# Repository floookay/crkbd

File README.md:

# Corne keyboard fork

The Corne keyboard is a split keyboard with 3x6 column staggered keys and 3 thumb keys,
based on [Helix](https://github.com/MakotoKurauchi/helix).
Crkbd stands for Corne Keyboard.

## Corne MX Low Profile

This fork altered the footprints of the Corne Classic to support Cherry MX Low Profile switches.  
For more information on how to build one see [here](./corne-mxlp/doc/buildguide_en.md)

### Compability

Despite the MX style stem of the switches these are not compatible with every MX style keycap. I included some more information in the build guide.

### RGB

The switches route the light of the RGB LEDs quite nicely imo: <https://imgur.com/7JVrjXo>

### PCB

I designed the footprint for the MXLP switch based on my measurements. The footprint file is included with the PCB. The switch has a tight fit.

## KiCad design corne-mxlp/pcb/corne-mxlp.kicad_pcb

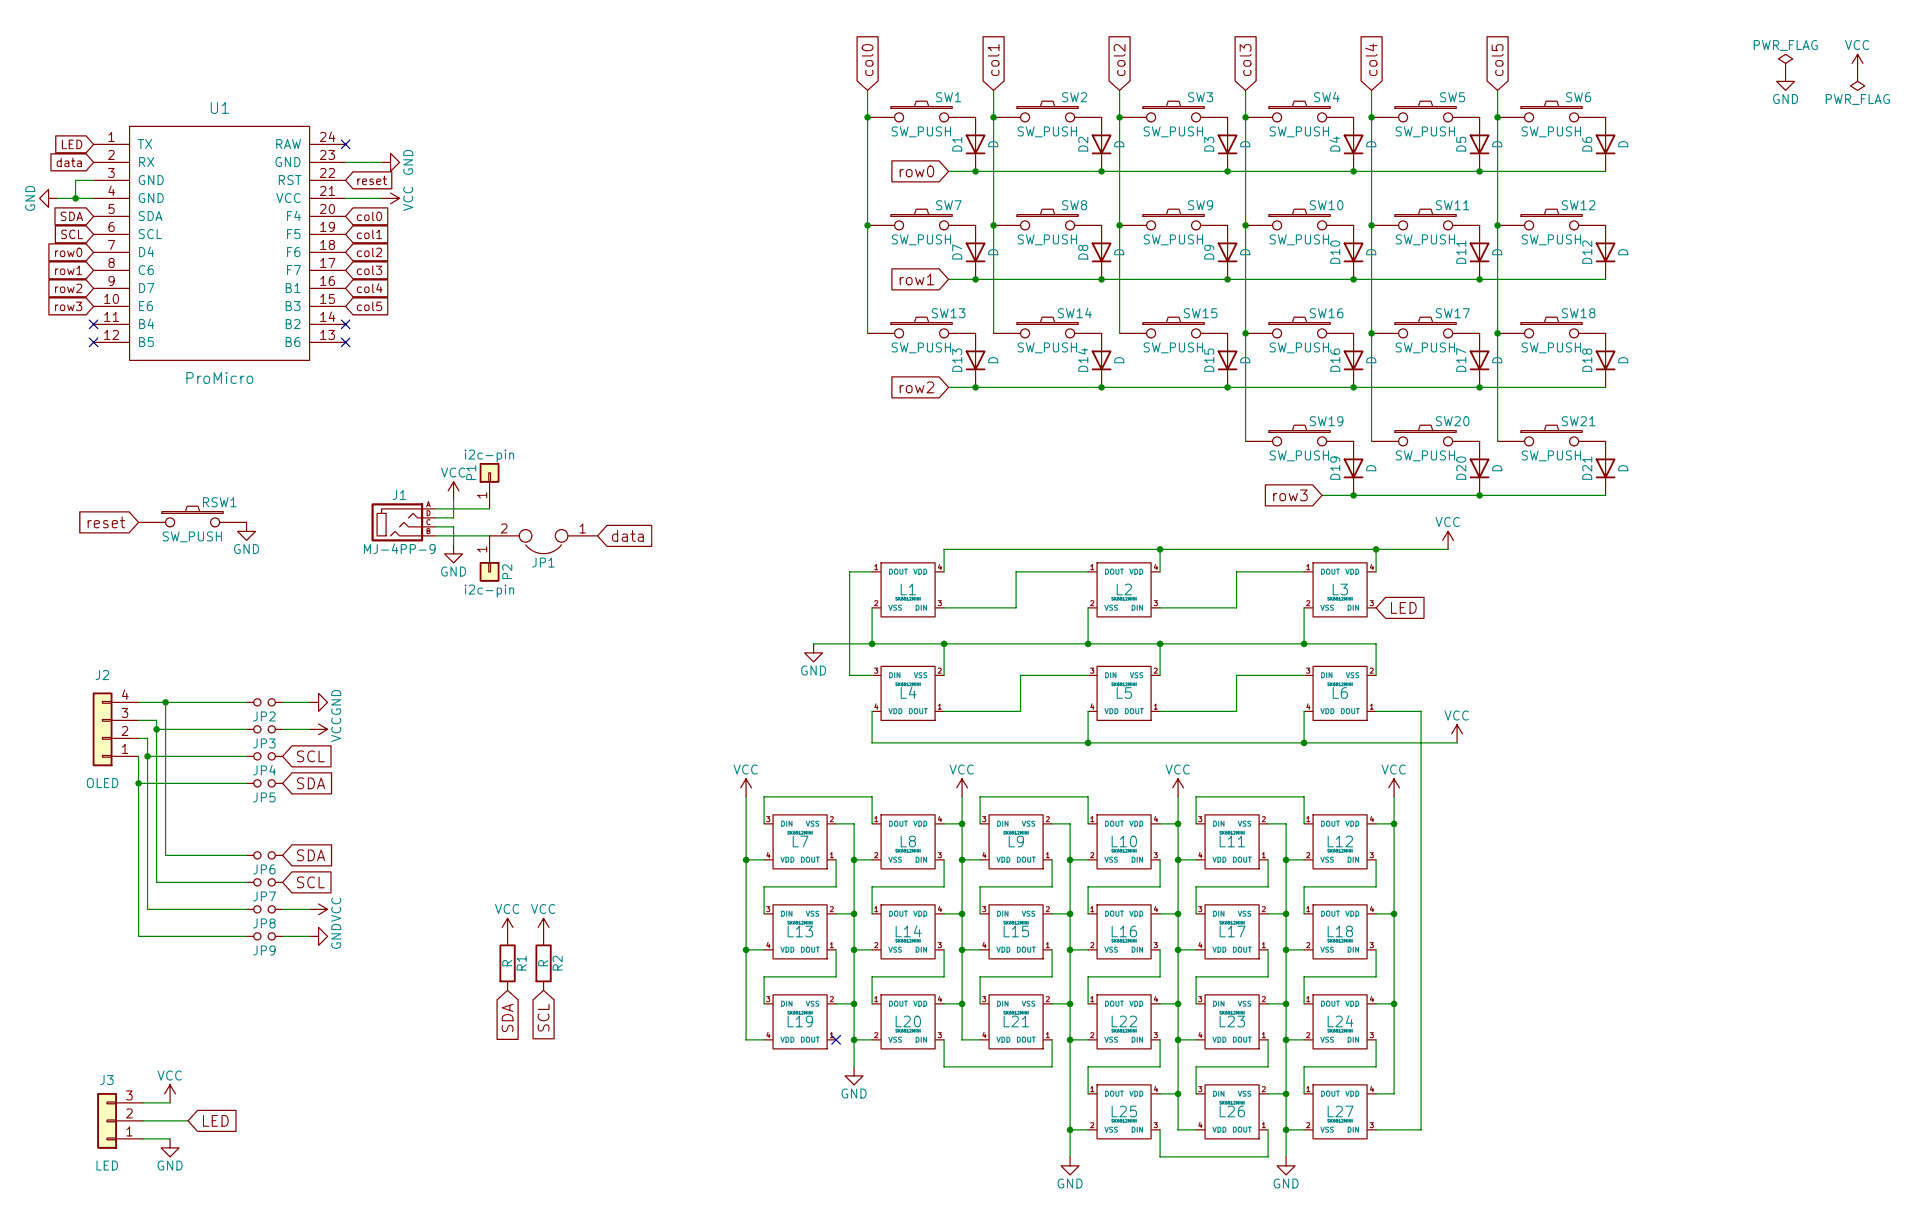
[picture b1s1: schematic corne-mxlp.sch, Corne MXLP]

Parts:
D1, D2, D3, D4, D5, D6, D7, D8, D9, D10, D11, D12, D13, D14, D15, D16, D17, D18, D19, D20, D21: D; D3_TH_SMD
J1: MJ-4PP-9
J2: OLED
J3: LED; StripLED_rev
JP1: JP
JP2, JP3, JP4, JP5, JP6, JP7, JP8, JP9: Jumper
L1, L2, L3, L4, L5, L6: SK6812MINI; SK6812MINI_underglow_rev
L7, L8, L9, L10, L11, L12, L13, L14, L15, L16, L17, L18, L19, L20, L21, L22, L23, L24, L25, L26, L27: SK6812MINI; SK6812MINI_rev
P1, P2: i2c-pin; 1pin_conn
R1, R2: R
RSW1: SW_PUSH; ResetSW
SW1, SW2, SW3, SW4, SW5, SW6, SW7, SW8, SW9, SW10, SW11, SW12, SW13, SW14, SW15, SW16, SW17, SW18, SW19, SW20, SW21: SW_PUSH; MXLP
U1: ProMicro; ProMicro_v2

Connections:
GND: J1.C, J3.1, JP2.1, JP9.1, L1.2 (VSS), L2.2 (VSS), L3.2 (VSS), L4.2 (VSS), L5.2 (VSS), L6.2 (VSS), L7.2 (VSS), L8.2 (VSS), L9.2 (VSS), L10.2 (VSS), L11.2 (VSS), L12.2 (VSS), L13.2 (VSS), L14.2 (VSS), L15.2 (VSS), L16.2 (VSS), L17.2 (VSS), L18.2 (VSS), L19.2 (VSS), L20.2 (VSS), L21.2 (VSS), L22.2 (VSS), L23.2 (VSS), L24.2 (VSS), L25.2 (VSS), L26.2 (VSS), L27.2 (VSS), RSW1.2, U1.3 (GND), U1.4 (GND), U1.23 (GND)
LED: J3.2, L3.3 (DIN), U1.1 (TX)
unnamed: D1.2 (A), SW1.2
unnamed: D2.2 (A), SW2.2
unnamed: D3.2 (A), SW3.2
unnamed: D4.2 (A), SW4.2
unnamed: D5.2 (A), SW5.2
unnamed: D6.2 (A), SW6.2
unnamed: D7.2 (A), SW7.2
unnamed: D8.2 (A), SW8.2
unnamed: D9.2 (A), SW9.2
unnamed: D10.2 (A), SW10.2
unnamed: D11.2 (A), SW11.2
unnamed: D12.2 (A), SW12.2
unnamed: D13.2 (A), SW13.2
unnamed: D14.2 (A), SW14.2
unnamed: D15.2 (A), SW15.2
unnamed: D16.2 (A), SW16.2
unnamed: D17.2 (A), SW17.2
unnamed: D18.2 (A), SW18.2
unnamed: D19.2 (A), SW19.2
unnamed: D20.2 (A), SW20.2
unnamed: D21.2 (A), SW21.2
unnamed: J1.A, P1.1
unnamed: J1.B, JP1.2, P2.1
unnamed: J2.1, JP5.2, JP9.2
unnamed: J2.2, JP4.2, JP8.2
unnamed: J2.3, JP3.2, JP7.2
unnamed: J2.4, JP2.2, JP6.2
unnamed: L1.1 (DOUT), L4.3 (DIN)
unnamed: L1.3 (DIN), L2.1 (DOUT)
unnamed: L2.3 (DIN), L3.1 (DOUT)
unnamed: L4.1 (DOUT), L5.3 (DIN)
unnamed: L5.1 (DOUT), L6.3 (DIN)
unnamed: L7.3 (DIN), L8.1 (DOUT)
unnamed: L9.3 (DIN), L10.1 (DOUT)
unnamed: L10.3 (DIN), L16.1 (DOUT)
unnamed: L11.1 (DOUT), L17.3 (DIN)
unnamed: L11.3 (DIN), L12.1 (DOUT)
unnamed: L12.3 (DIN), L18.1 (DOUT)
unnamed: L13.1 (DOUT), L19.3 (DIN)
unnamed: L7.1 (DOUT), L13.3 (DIN)
unnamed: L8.3 (DIN), L14.1 (DOUT)
unnamed: L14.3 (DIN), L20.1 (DOUT)
unnamed: L15.1 (DOUT), L21.3 (DIN)
unnamed: L9.1 (DOUT), L15.3 (DIN)
unnamed: L16.3 (DIN), L22.1 (DOUT)
unnamed: L17.1 (DOUT), L23.3 (DIN)
unnamed: L18.3 (DIN), L24.1 (DOUT)
unnamed: L20.3 (DIN), L21.1 (DOUT)
unnamed: L22.3 (DIN), L25.1 (DOUT)
unnamed: L23.1 (DOUT), L26.3 (DIN)
unnamed: L24.3 (DIN), L27.1 (DOUT)
unnamed: L25.3 (DIN), L26.1 (DOUT)
unnamed: L6.1 (DOUT), L27.3 (DIN)
SCL: JP4.1, JP7.1, R2.2, U1.6 (SCL)
SDA: JP5.1, JP6.1, R1.2, U1.5 (SDA)
VCC: J1.D, J3.3, JP3.1, JP8.1, L1.4 (VDD), L2.4 (VDD), L3.4 (VDD), L4.4 (VDD), L5.4 (VDD), L6.4 (VDD), L7.4 (VDD), L8.4 (VDD), L9.4 (VDD), L10.4 (VDD), L11.4 (VDD), L12.4 (VDD), L13.4 (VDD), L14.4 (VDD), L15.4 (VDD), L16.4 (VDD), L17.4 (VDD), L18.4 (VDD), L19.4 (VDD), L20.4 (VDD), L21.4 (VDD), L22.4 (VDD), L23.4 (VDD), L24.4 (VDD), L25.4 (VDD), L26.4 (VDD), L27.4 (VDD), R1.1, R2.1, U1.21 (VCC)
col0: SW1.1, SW7.1, SW13.1, U1.20 (F4)
col1: SW2.1, SW8.1, SW14.1, U1.19 (F5)
col2: SW3.1, SW9.1, SW15.1, U1.18 (F6)
col3: SW4.1, SW10.1, SW16.1, SW19.1, U1.17 (F7)
col4: SW5.1, SW11.1, SW17.1, SW20.1, U1.16 (B1)
col5: SW6.1, SW12.1, SW18.1, SW21.1, U1.15 (B3)
data: JP1.1, U1.2 (RX)
reset: RSW1.1, U1.22 (RST)
row0: D1.1 (K), D2.1 (K), D3.1 (K), D4.1 (K), D5.1 (K), D6.1 (K), U1.7 (D4)
row1: D7.1 (K), D8.1 (K), D9.1 (K), D10.1 (K), D11.1 (K), D12.1 (K), U1.8 (C6)
row2: D13.1 (K), D14.1 (K), D15.1 (K), D16.1 (K), D17.1 (K), D18.1 (K), U1.9 (D7)
row3: D19.1 (K), D20.1 (K), D21.1 (K), U1.10 (E6)

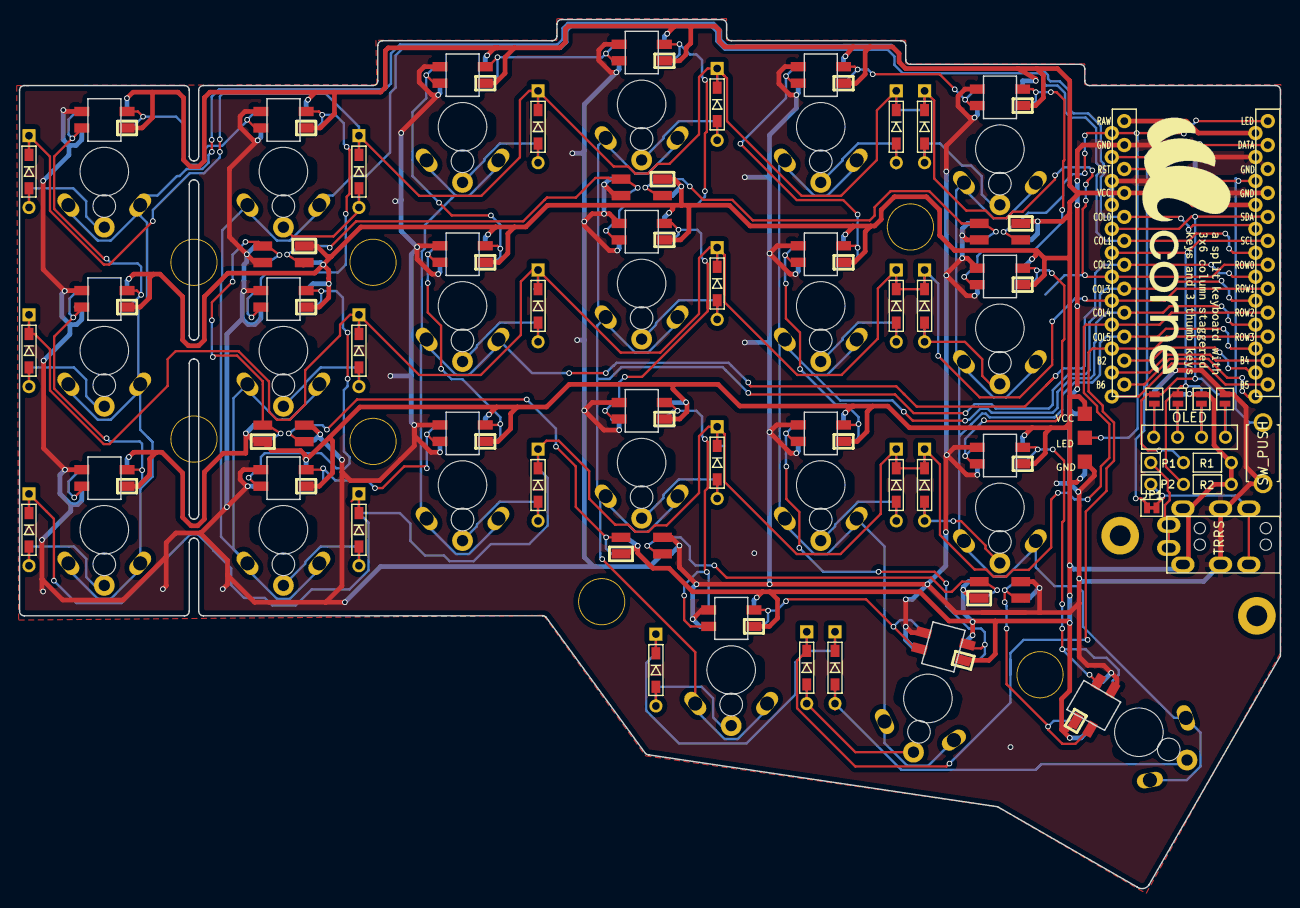
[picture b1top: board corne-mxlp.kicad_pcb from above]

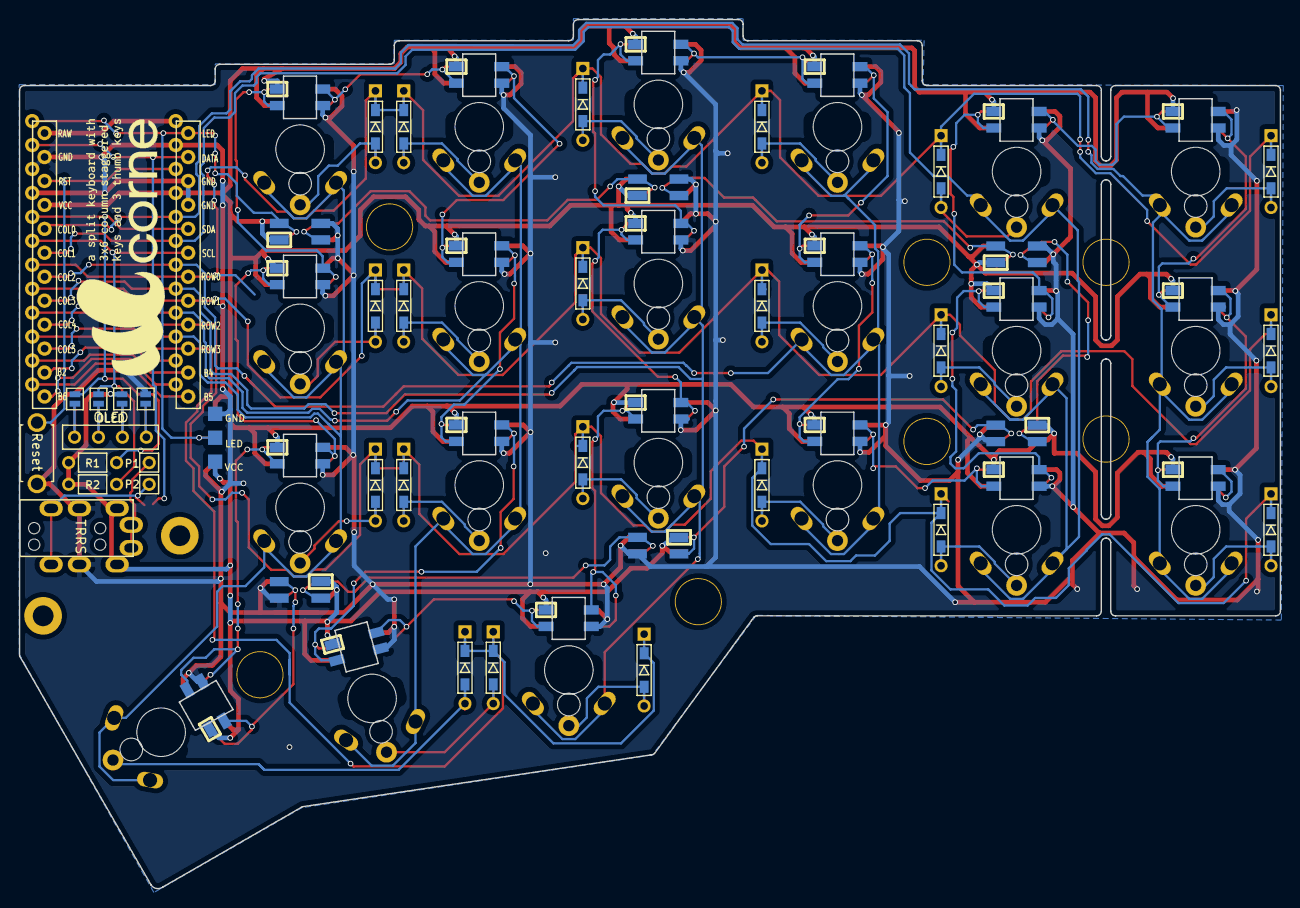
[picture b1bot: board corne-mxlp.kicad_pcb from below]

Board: 2 copper layers, 133.8 x 92.2 mm, 87 parts (4 on the bottom side), 70 nets.

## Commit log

2021-01-31 added Corne MXLP files + build guide
